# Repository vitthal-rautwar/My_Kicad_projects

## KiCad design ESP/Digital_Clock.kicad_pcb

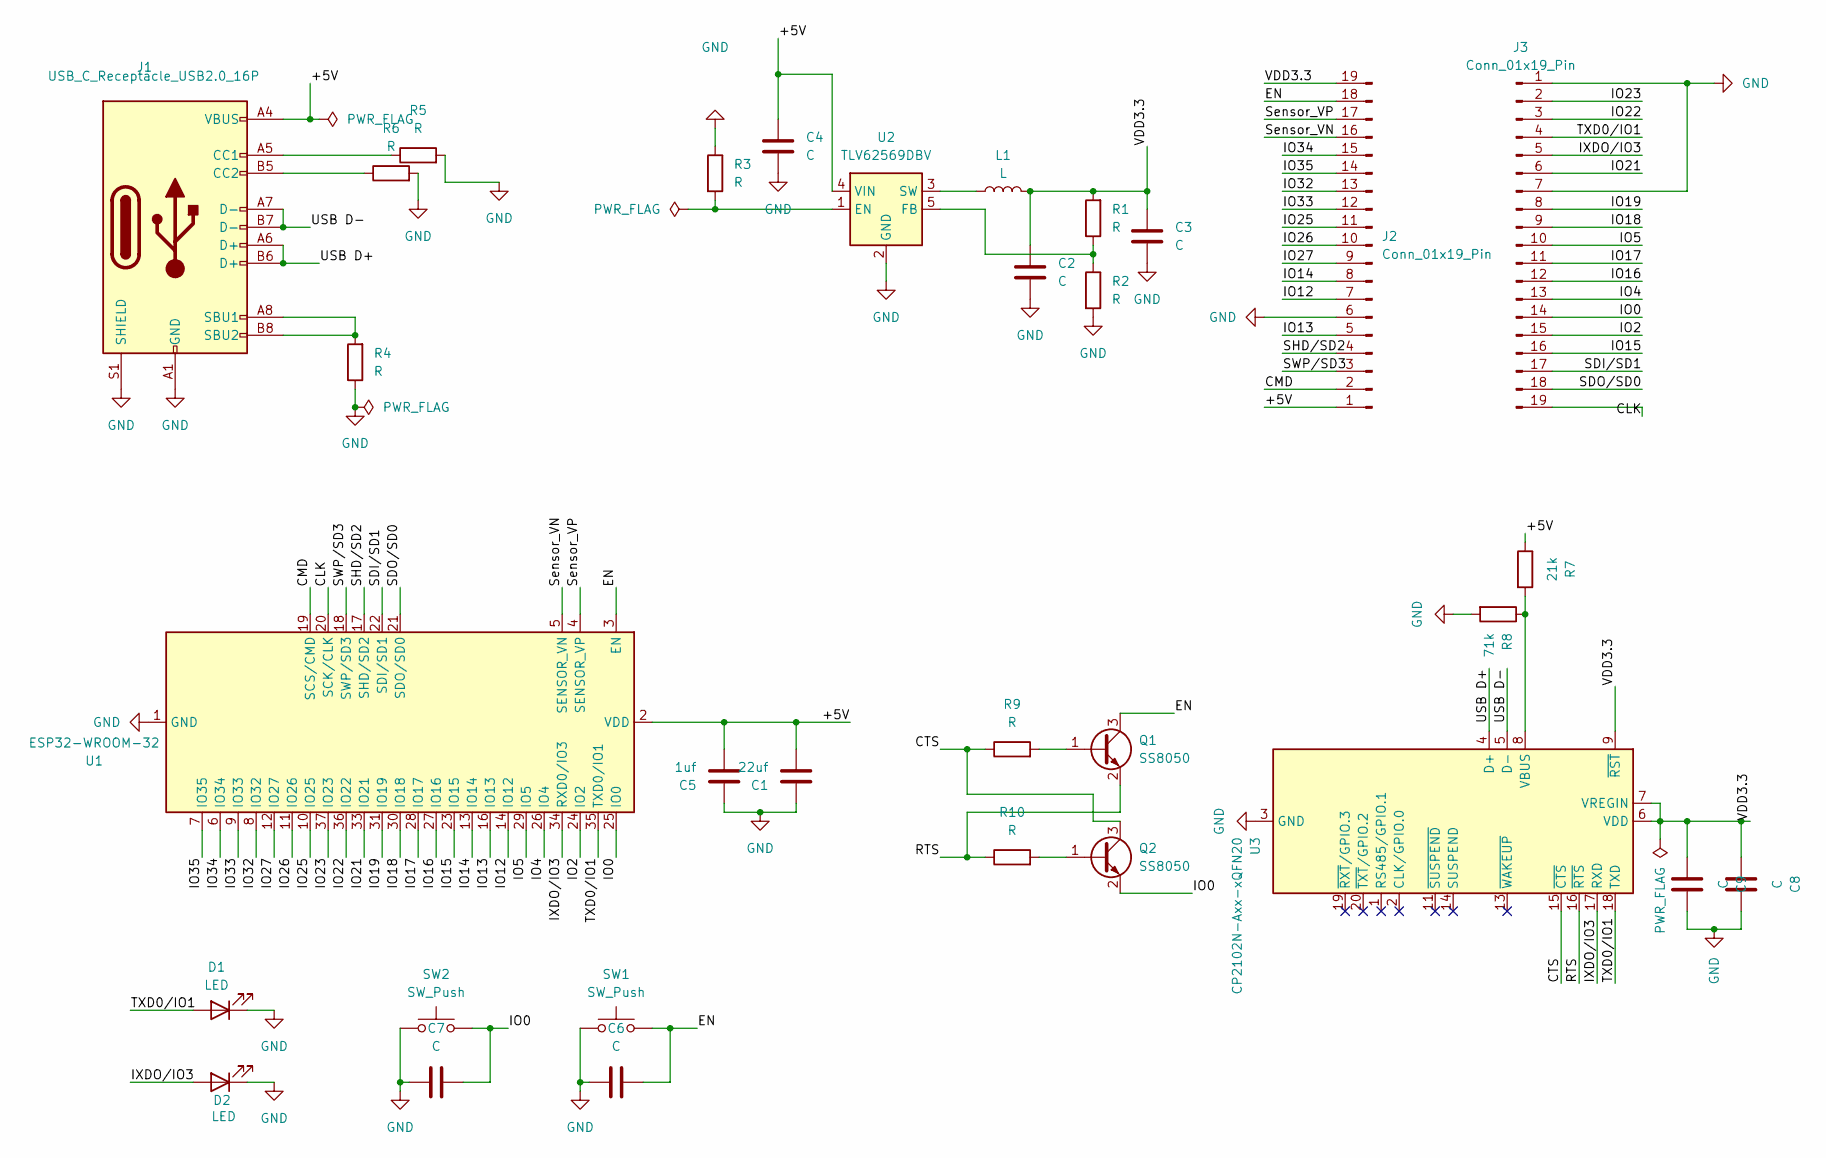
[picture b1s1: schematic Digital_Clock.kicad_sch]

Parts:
C1: 22uf; C_0201_0603Metric_Pad0.64x0.40mm_HandSolder
C2, C3, C7, C8, C9: C; C_0201_0603Metric_Pad0.64x0.40mm_HandSolder
C4, C6: C; C_0402_1005Metric
C5: 1uf; C_0201_0603Metric_Pad0.64x0.40mm_HandSolder
D1, D2: LED; LED_0603_1608Metric
J1: USB_C_Receptacle_USB2.0_16P; USB_C_Receptacle_G-Switch_GT-USB-7010ASV
J2, J3: Conn_01x19_Pin; PinHeader_1x19_P2.54mm_Vertical
L1: L; L_0402_1005Metric
Q1, Q2: SS8050; SOT-23
R1, R2, R3, R9, R10: R; R_0402_1005Metric
R4, R5, R6: R; R_0603_1608Metric_Pad0.98x0.95mm_HandSolder
R7: 21k; R_0402_1005Metric
R8: 71k; R_0402_1005Metric
SW1, SW2: SW_Push; SW_SPST_B3U-1000P
U1: ESP32-WROOM-32
U2: TLV62569DBV; SOT-23-5
U3: CP2102N-Axx-xQFN20; SiliconLabs_QFN-20-1EP_3x3mm_P0.5mm_EP1.8x1.8mm

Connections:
/+5V: C1.2, C4.1, C5.2, J1.A4 (VBUS), J1.A9 (VBUS), J1.B4 (VBUS), J1.B9 (VBUS), J2.1, R7.1, U1.2 (VDD), U2.4 (VIN)
/CLK: J3.19, U1.20 (SCK/CLK)
/CMD: J2.2, U1.19 (SCS/CMD)
/CTS: Q2.3 (C), R9.1, U3.15 (~CTS)
/EN: C6.1, J2.18, Q1.3 (C), SW1.2, U1.3 (EN)
/IO0: C7.2, J3.14, Q2.2 (E), SW2.2, U1.25 (IO0)
/IO2: J3.15, U1.24 (IO2)
/IO4: J3.13, U1.26 (IO4)
/IO5: J3.10, U1.29 (IO5)
/IO12: J2.7, U1.14 (IO12)
/IO13: J2.5, U1.16 (IO13)
/IO14: J2.8, U1.13 (IO14)
/IO15: J3.16, U1.23 (IO15)
/IO16: J3.12, U1.27 (IO16)
/IO17: J3.11, U1.28 (IO17)
/IO18: J3.9, U1.30 (IO18)
/IO19: J3.8, U1.31 (IO19)
/IO21: J3.6, U1.33 (IO21)
/IO22: J3.3, U1.36 (IO22)
/IO23: J3.2, U1.37 (IO23)
/IO25: J2.11, U1.10 (IO25)
/IO26: J2.10, U1.11 (IO26)
/IO27: J2.9, U1.12 (IO27)
/IO32: J2.13, U1.8 (IO32)
/IO33: J2.12, U1.9 (IO33)
/IO34: J2.15, U1.6 (IO34)
/IO35: J2.14, U1.7 (IO35)
/IXDO/IO3: D2.2 (A), J3.5, U1.34 (RXD0/IO3), U3.17 (RXD)
/RTS: Q1.2 (E), R10.1, U3.16 (~RTS)
/SDI/SD1: J3.17, U1.22 (SDI/SD1)
/SDO/SD0: J3.18, U1.21 (SDO/SD0)
/SHD/SD2: J2.4, U1.17 (SHD/SD2)
/SWP/SD3: J2.3, U1.18 (SWP/SD3)
/Sensor_VN: J2.16, U1.5 (SENSOR_VN)
/Sensor_VP: J2.17, U1.4 (SENSOR_VP)
/TXD0/IO1: D1.2 (A), J3.4, U1.35 (TXD0/IO1), U3.18 (TXD)
/USB D+: J1.A6 (D+), J1.B6 (D+), U3.4 (D+)
/USB D-: J1.A7 (D-), J1.B7 (D-), U3.5 (D-)
/VDD3.3: C2.1, C3.1, C8.1, C9.1, J2.19, L1.2, R1.2, U3.6 (VDD), U3.7 (VREGIN), U3.9 (~RST)
GND: C1.1, C2.2, C3.2, C4.2, C5.1, C6.2, C7.1, C8.2, C9.2, D1.1 (K), D2.1 (K), J1.A1 (GND), J1.A12 (GND), J1.B1 (GND), J1.B12 (GND), J1.S1 (SHIELD), J2.6, J3.1, J3.7, R2.2, R3.1, R4.1, R5.2, R6.2, R8.2, SW1.1, SW2.1, U1.1 (GND), U1.15 (GND), U1.38 (GND), U1.39 (GND), U2.2 (GND), U3.3 (GND), U3.12 (GND), U3.21 (GND)
unnamed: J1.A5 (CC1), R5.1
unnamed: J1.B5 (CC2), R6.1
unnamed: J1.A8 (SBU1), J1.B8 (SBU2), R4.2
unnamed: Q1.1 (B), R9.2
unnamed: Q2.1 (B), R10.2
unnamed: R3.2, U2.1 (EN)
unnamed: R1.1, R2.1, U2.5 (FB)
unnamed: L1.1, U2.3 (SW)
unnamed: R7.2, R8.1, U3.8 (VBUS)

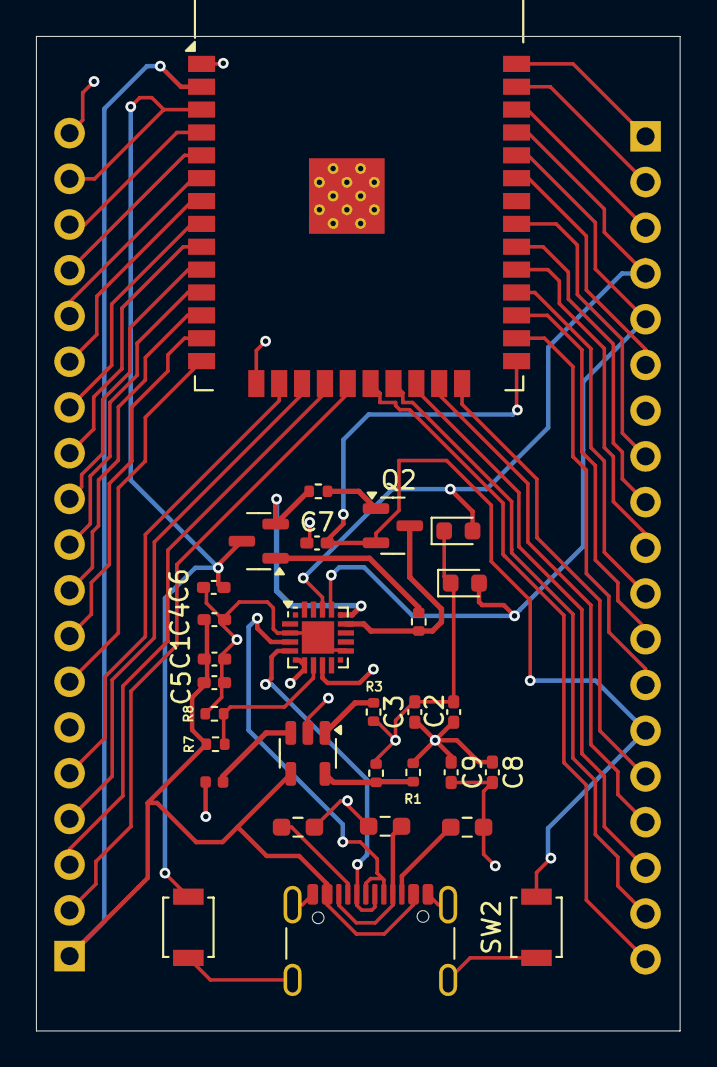
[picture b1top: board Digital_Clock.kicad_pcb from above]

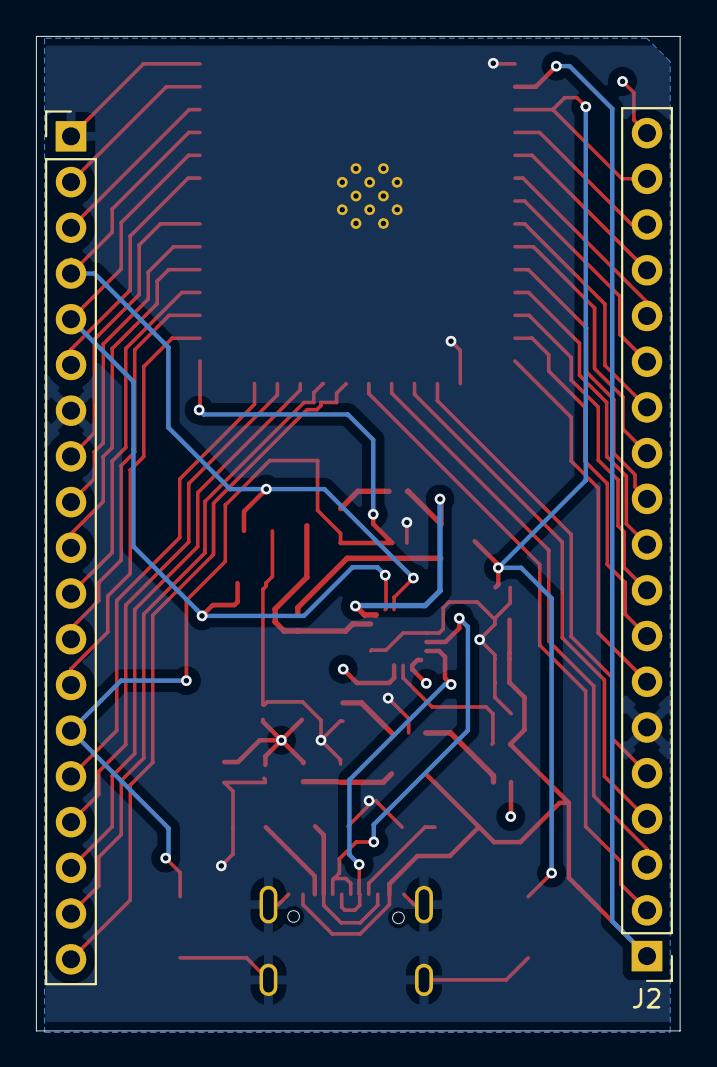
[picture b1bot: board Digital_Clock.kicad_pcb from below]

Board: 4 copper layers, 35.8 x 55.2 mm, 32 parts (2 on the bottom side), 49 nets.

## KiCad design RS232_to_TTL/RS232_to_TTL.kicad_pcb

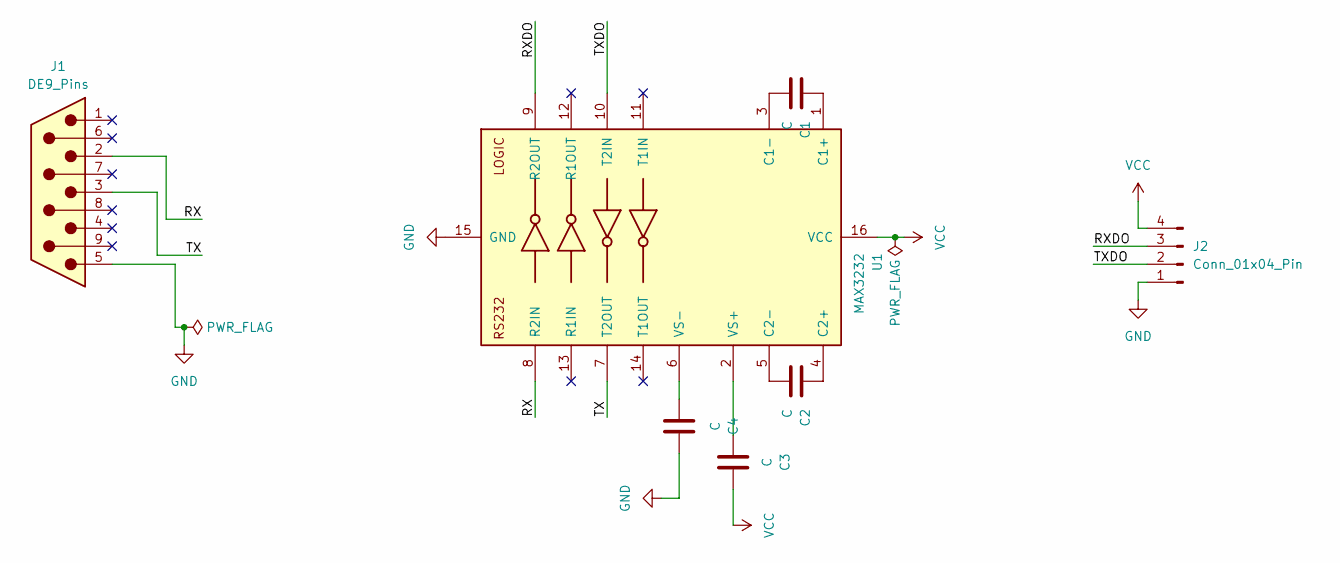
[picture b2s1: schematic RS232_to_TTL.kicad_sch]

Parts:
C1, C2, C3, C4: C; C_0402_1005Metric_Pad0.74x0.62mm_HandSolder
J1: DE9_Pins; DSUB-9_Pins_Horizontal_P2.77x2.54mm_EdgePinOffset9.40mm
J2: Conn_01x04_Pin; PinHeader_1x04_P2.54mm_Vertical
U1: MAX3232; SOIC-16_4.55x10.3mm_P1.27mm

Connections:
/RX: J1.2, U1.8 (R2IN)
/RXDO: J2.3, U1.9 (R2OUT)
/TX: J1.3, U1.7 (T2OUT)
/TXDO: J2.2, U1.10 (T2IN)
GND: C4.2, J1.5, J2.1, U1.15 (GND)
unnamed: C1.1, U1.1 (C1+)
unnamed: C1.2, U1.3 (C1-)
unnamed: C2.1, U1.4 (C2+)
unnamed: C2.2, U1.5 (C2-)
unnamed: C3.1, U1.2 (VS+)
unnamed: C4.1, U1.6 (VS-)
VCC: C3.2, J2.4, U1.16 (VCC)

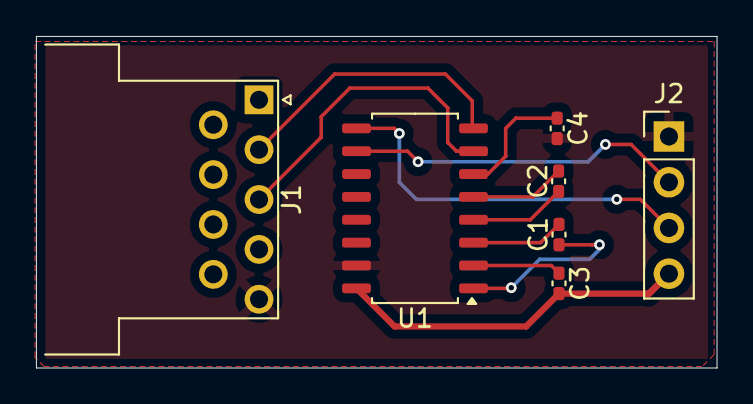
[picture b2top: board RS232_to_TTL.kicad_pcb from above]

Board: 2 copper layers, 37.8 x 18.4 mm, 7 parts (0 on the bottom side), 12 nets.

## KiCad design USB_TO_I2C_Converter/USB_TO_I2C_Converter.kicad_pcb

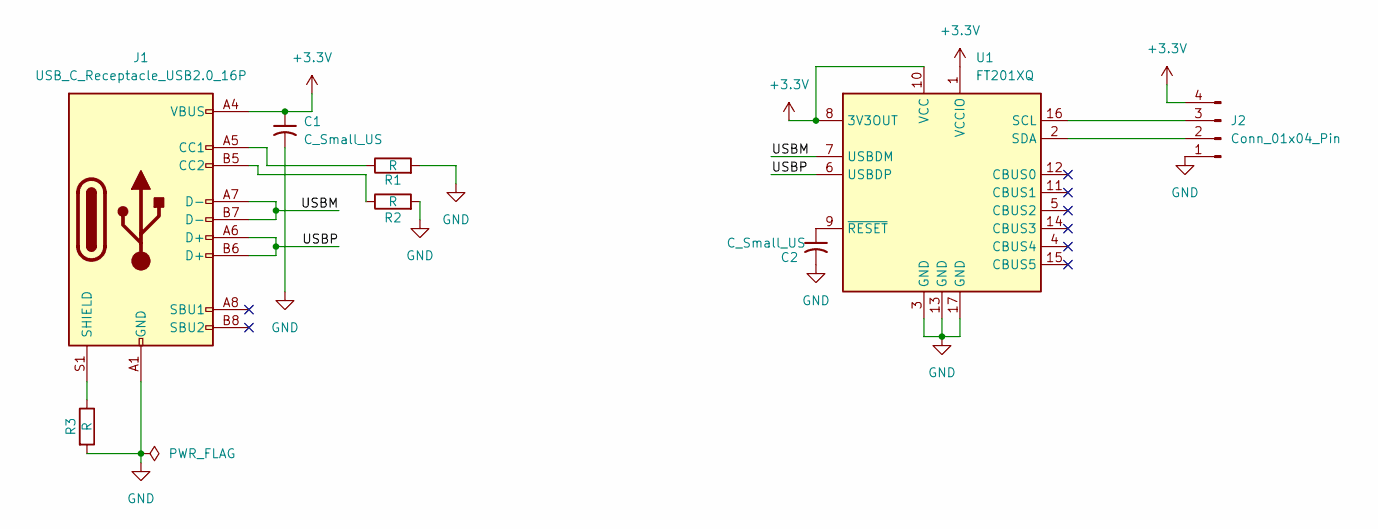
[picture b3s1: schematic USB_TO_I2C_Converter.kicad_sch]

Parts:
C1, C2: C_Small_US; C_0402_1005Metric_Pad0.74x0.62mm_HandSolder
J1: USB_C_Receptacle_USB2.0_16P; USB_C_Receptacle_GCT_USB4105-xx-A_16P_TopMnt_Horizontal
J2: Conn_01x04_Pin; PinHeader_1x04_P2.54mm_Vertical
R1, R2, R3: R; R_0402_1005Metric
U1: FT201XQ; QFN-16-1EP_4x4mm_P0.65mm_EP2.1x2.1mm

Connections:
+3.3V: C1.1, J1.A4 (VBUS), J1.A9 (VBUS), J1.B4 (VBUS), J1.B9 (VBUS), J2.4, U1.1 (VCCIO), U1.8 (3V3OUT), U1.10 (VCC)
/USBM: J1.A7 (D-), J1.B7 (D-), U1.7 (USBDM)
/USBP: J1.A6 (D+), J1.B6 (D+), U1.6 (USBDP)
GND: C1.2, C2.2, J1.A1 (GND), J1.A12 (GND), J1.B1 (GND), J1.B12 (GND), J2.1, R1.2, R2.2, R3.2, U1.3 (GND), U1.13 (GND), U1.17 (GND)
unnamed: J1.A5 (CC1), R1.1
unnamed: J1.B5 (CC2), R2.1
unnamed: J1.S1 (SHIELD), R3.1
unnamed: J2.2, U1.2 (SDA)
unnamed: J2.3, U1.16 (SCL)
unnamed: C2.1, U1.9 (~RESET)

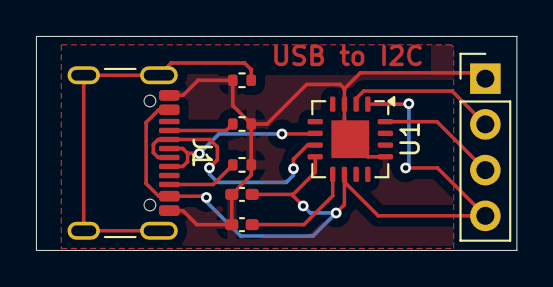
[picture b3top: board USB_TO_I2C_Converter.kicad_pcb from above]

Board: 2 copper layers, 26.7 x 11.9 mm, 8 parts (0 on the bottom side), 10 nets.
